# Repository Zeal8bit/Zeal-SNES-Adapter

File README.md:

## SNES controller adapter for Zeal 8-bit Computer

The goal of this project is to create an SNES controller adapter PCB for Zeal 8-bit Computer.

This repository includes:
* An example/driver written in Z80 assembly to communicate with the adapter
* A Kicad (v6) project for the PCB board
* Gerber files for PCB. If you don't want or can't open the Kicad project and generate gerber files, you can directly download the gerber files and send them to your favorite PCB manufacturer.

## License

Distributed under the Apache 2.0 License. See LICENSE file for more information.

You are free to use it for personal and commercial use, the boilerplate present in each file must not be removed.

## Contact

For any suggestion or request, you can contact me at contact [at] zeal8bit [dot] com or on the Discord server https://discord.gg/UzEjwRvBBb

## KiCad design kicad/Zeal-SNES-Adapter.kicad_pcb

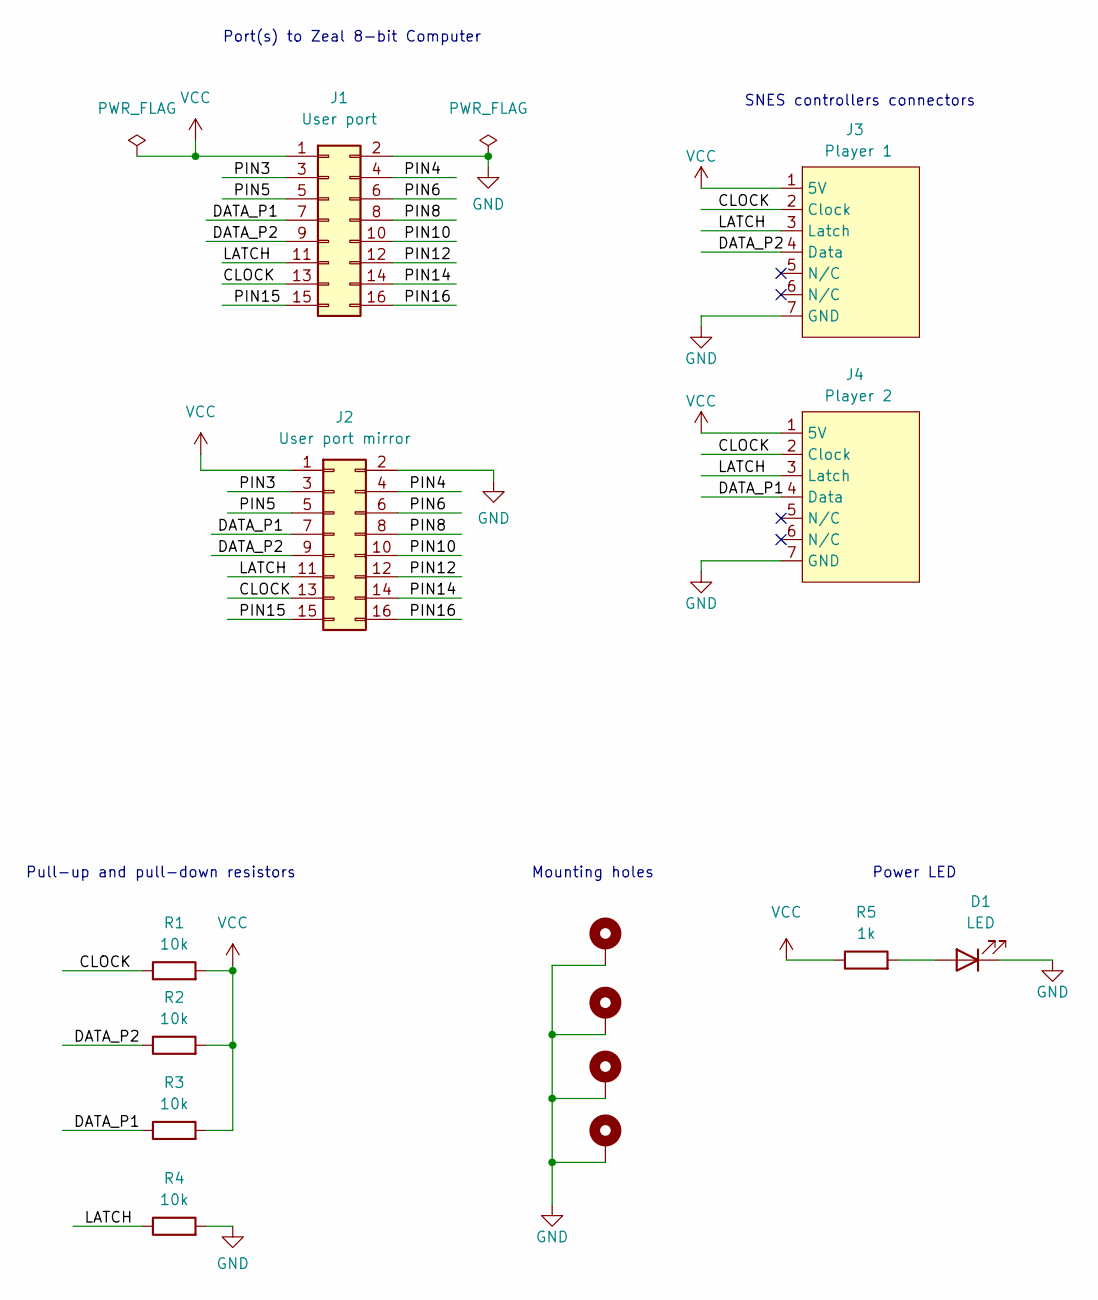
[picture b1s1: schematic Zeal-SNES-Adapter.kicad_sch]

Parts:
D1: LED; LED_D5.0mm
H1, H2, H3, H4: MountingHole_Pad; MountingHole_2.2mm_M2_Pad
J1: User port; PinHeader_2x08_P2.54mm_Horizontal
J2: User port mirror; PinHeader_2x08_P2.54mm_Vertical
J3: Player 1; SNES
J4: Player 2; SNES
R1, R2, R3, R4: 10k; R_Axial_DIN0207_L6.3mm_D2.5mm_P10.16mm_Horizontal
R5: 1k; R_Axial_DIN0207_L6.3mm_D2.5mm_P10.16mm_Horizontal

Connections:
/CLOCK: J1.13, J2.13, J3.2 (Clock), J4.2 (Clock), R1.1
/DATA_P1: J1.7, J2.7, J4.4 (Data), R3.1
/DATA_P2: J1.9, J2.9, J3.4 (Data), R2.1
/LATCH: J1.11, J2.11, J3.3 (Latch), J4.3 (Latch), R4.1
/PIN3: J1.3, J2.3
/PIN4: J1.4, J2.4
/PIN5: J1.5, J2.5
/PIN6: J1.6, J2.6
/PIN8: J1.8, J2.8
/PIN10: J1.10, J2.10
/PIN12: J1.12, J2.12
/PIN14: J1.14, J2.14
/PIN15: J1.15, J2.15
/PIN16: J1.16, J2.16
GND: D1.1 (K), H1.1, H2.1, H3.1, H4.1, J1.2, J2.2, J3.7 (GND), J4.7 (GND), R4.2
unnamed: D1.2 (A), R5.2
VCC: J1.1, J2.1, J3.1 (5V), J4.1 (5V), R1.2, R2.2, R3.2, R5.1

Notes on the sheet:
Mounting holes
Power LED
SNES controllers connectors
Pull-up and pull-down resistors
Port(s) to Zeal 8-bit Computer

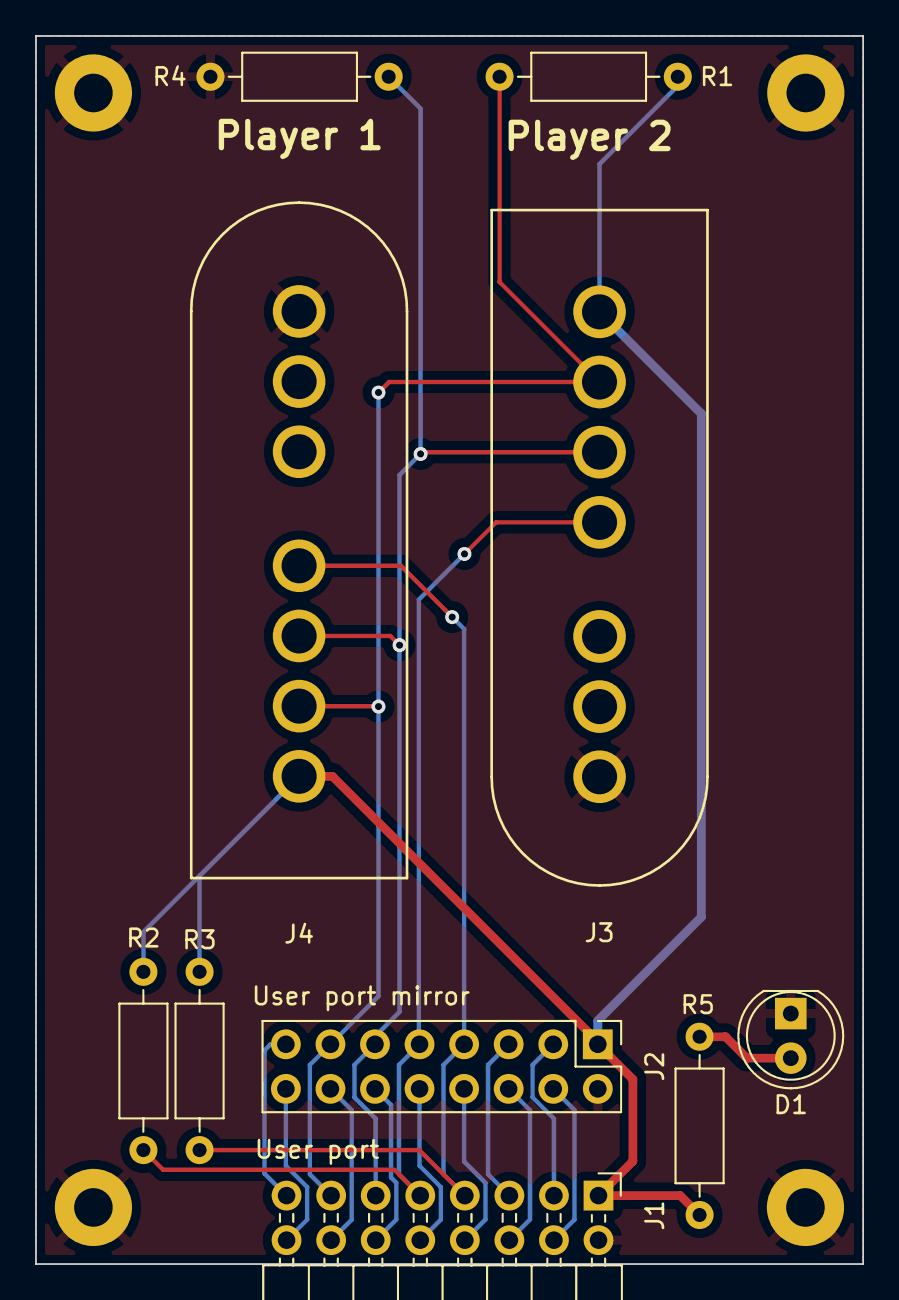
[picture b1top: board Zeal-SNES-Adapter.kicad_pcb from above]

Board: 2 copper layers, 47.1 x 70.0 mm, 14 parts (0 on the bottom side), 17 nets.

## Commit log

2022-10-23 Add the SNES controller driver/example, written in Z80 assembly
2022-10-23 PCB: Add kicad project and gerber files
2022-10-23 README: Add more info about the project
